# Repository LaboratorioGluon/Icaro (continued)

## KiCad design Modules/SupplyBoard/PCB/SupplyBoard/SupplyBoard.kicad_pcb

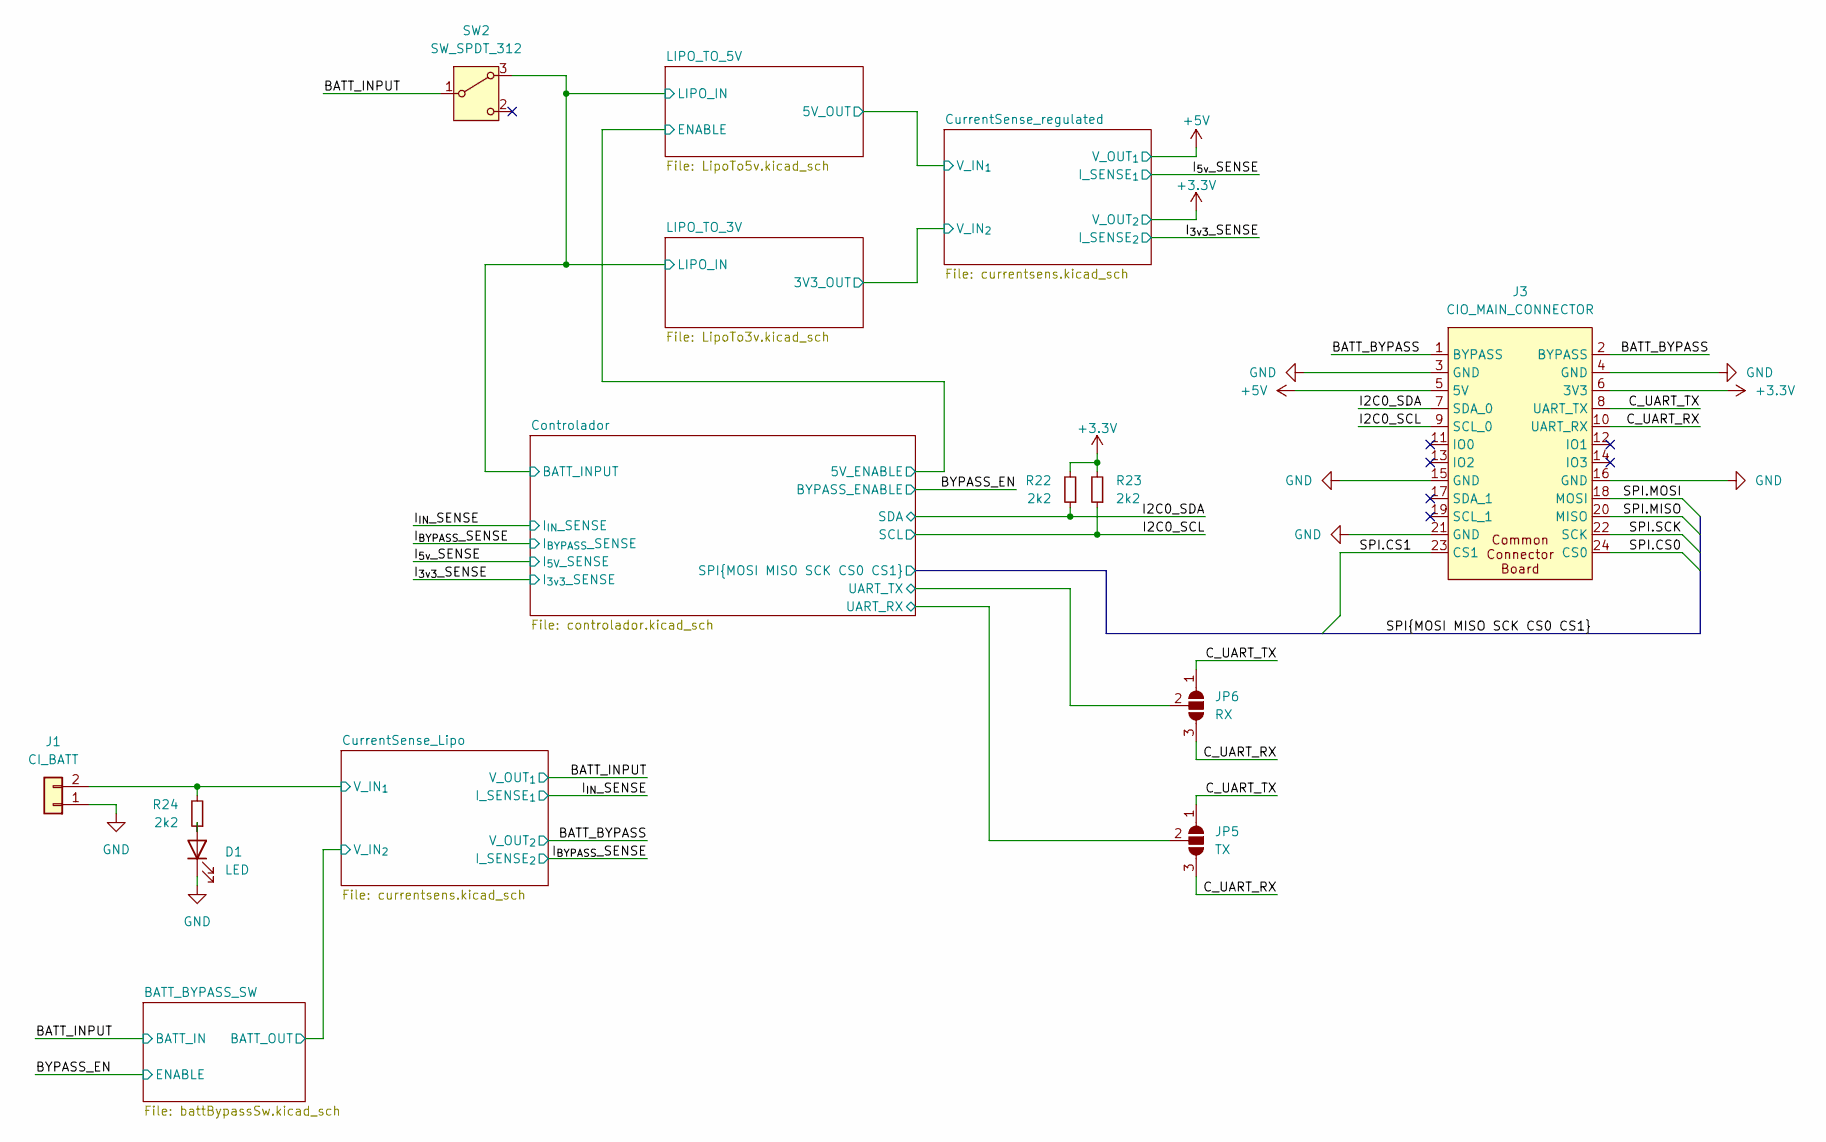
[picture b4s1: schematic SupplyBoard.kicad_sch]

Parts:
D1: LED; LED_0805_2012Metric_Pad1.15x1.40mm_HandSolder
J1: CI_BATT; AMASS_XT30U-F_1x02_P5.0mm_Vertical
J3: CIO_MAIN_CONNECTOR; Connector_Icaro_Edge_tarjeta
JP5: TX; SolderJumper-3_P1.3mm_Open_Pad1.0x1.5mm
JP6: RX; SolderJumper-3_P1.3mm_Open_Pad1.0x1.5mm
R22, R23, R24: 2k2; R_0603_1608Metric_Pad0.98x0.95mm_HandSolder
SW2: SW_SPDT_312; PinHeader_1x03_P2.00mm_Vertical

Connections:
+5V: J3.5 (5V); also elsewhere on the board
/BATT_BYPASS: J3.1 (BYPASS), J3.2 (BYPASS); also elsewhere on the board
/BATT_INPUT: SW2.1 (B); also elsewhere on the board
/C_UART_RX: J3.10 (UART_RX), JP5.3 (B), JP6.3 (B)
/C_UART_TX: J3.8 (UART_TX), JP5.1 (A), JP6.1 (A)
/Controlador/BATT_INPUT: SW2.3 (A); also elsewhere on the board
/Controlador/UART_RX: JP5.2 (C); also elsewhere on the board
/Controlador/UART_TX: JP6.2 (C); also elsewhere on the board
/CurrentSense_Lipo/V_IN_{1}: J1.2, R24.2; also elsewhere on the board
/I2C0_SCL: J3.9 (SCL_0), R23.1; also elsewhere on the board
/I2C0_SDA: J3.7 (SDA_0), R22.1; also elsewhere on the board
/SPI.CS0: J3.24 (CS0); also elsewhere on the board
/SPI.CS1: J3.23 (CS1); also elsewhere on the board
/SPI.MISO: J3.20 (MISO); also elsewhere on the board
/SPI.MOSI: J3.18 (MOSI); also elsewhere on the board
/SPI.SCK: J3.22 (SCK); also elsewhere on the board
GND: D1.1 (K), J1.1, J3.3 (GND), J3.4 (GND), J3.15 (GND), J3.16 (GND), J3.21 (GND); also elsewhere on the board
unnamed: D1.2 (A), R24.1

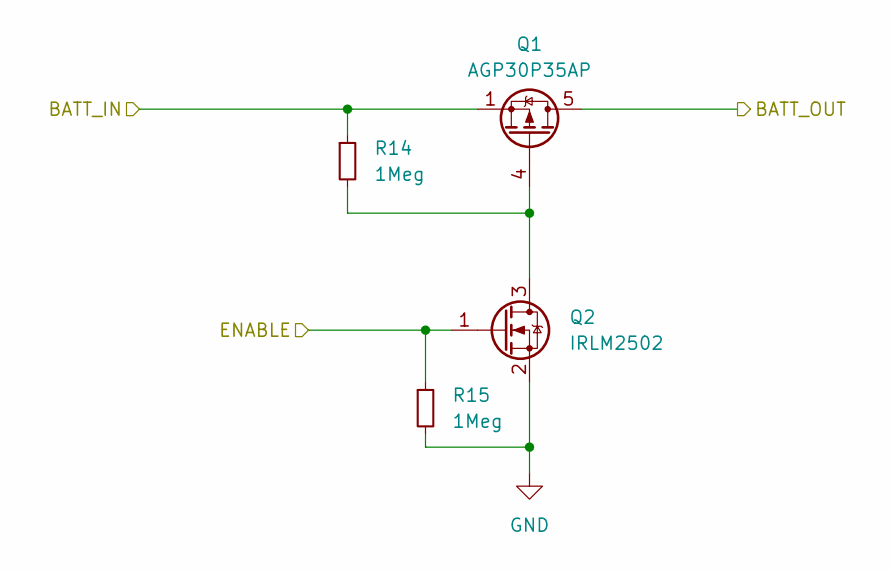
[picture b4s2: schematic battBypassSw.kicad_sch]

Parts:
Q1: AGP30P35AP; Diodes_PowerDI3333-8; LCSC C19633870
Q2: IRLM2502; SOT-23
R14, R15: 1Meg; R_0603_1608Metric_Pad0.98x0.95mm_HandSolder

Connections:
/BATT_BYPASS_SW/BATT_OUT: Q1.5 (D); also elsewhere on the board
/BATT_INPUT: Q1.1 (S), Q1.2 (S), Q1.3 (S), R14.1; also elsewhere on the board
/BYPASS_EN: Q2.1 (G), R15.1; also elsewhere on the board
GND: Q2.2 (S), R15.2; also elsewhere on the board
unnamed: Q1.4 (G), Q2.3 (D), R14.2

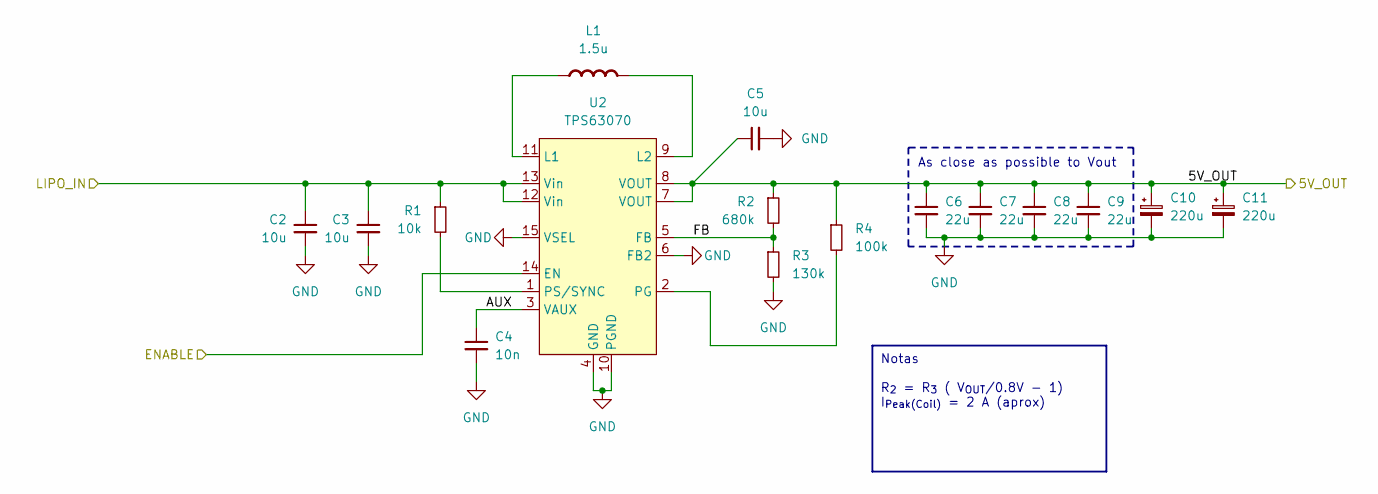
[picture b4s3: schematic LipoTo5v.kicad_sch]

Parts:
C2: 10u; C_0603_1608Metric_Pad1.08x0.95mm_HandSolder; LCSC C6119887
C3, C5: 10u; C_0603_1608Metric_Pad1.08x0.95mm_HandSolder
C4: 10n; C_0603_1608Metric_Pad1.08x0.95mm_HandSolder
C6, C7, C8, C9: 22u; C_0603_1608Metric_Pad1.08x0.95mm_HandSolder
C10, C11: 220u; CP_EIA-3216-18_Kemet-A_Pad1.58x1.35mm_HandSolder
L1: 1.5u; L_Coilcraft_XxL4040; Rating A; LCSC C5289354
R1: 10k; R_0603_1608Metric_Pad0.98x0.95mm_HandSolder
R2: 680k; R_0603_1608Metric_Pad0.98x0.95mm_HandSolder
R3: 130k; R_0603_1608Metric_Pad0.98x0.95mm_HandSolder
R4: 100k; R_0603_1608Metric_Pad0.98x0.95mm_HandSolder
U2: TPS63070; RNM0015A

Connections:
/Controlador/5V_ENABLE: U2.14 (EN); also elsewhere on the board
/Controlador/BATT_INPUT: C2.1, C3.1, R1.1, U2.12 (Vin), U2.13 (Vin); also elsewhere on the board
/LIPO_TO_5V/5V_OUT: C5.1, C6.1, C7.1, C8.1, C9.1, C10.1, C11.1, R2.1, R4.1, U2.7 (VOUT), U2.8 (VOUT); also elsewhere on the board
/LIPO_TO_5V/AUX: C4.1, U2.3 (VAUX)
/LIPO_TO_5V/FB: R2.2, R3.1, U2.5 (FB)
GND: C2.2, C3.2, C4.2, C5.2, C6.2, C7.2, C8.2, C9.2, C10.2, C11.2, R3.2, U2.4 (GND), U2.6 (FB2), U2.10 (PGND), U2.15 (VSEL); also elsewhere on the board
unnamed: L1.1 (+), U2.11 (L1)
unnamed: L1.2 (-), U2.9 (L2)
unnamed: R4.2, U2.2 (PG)
unnamed: R1.2, U2.1 (PS/SYNC)

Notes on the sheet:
As close as possible to Vout
Notas R_{2} = R_{3} ( V_{OUT}/0.8V - 1) I_{Peak(Coil)} = 2 A (aprox)

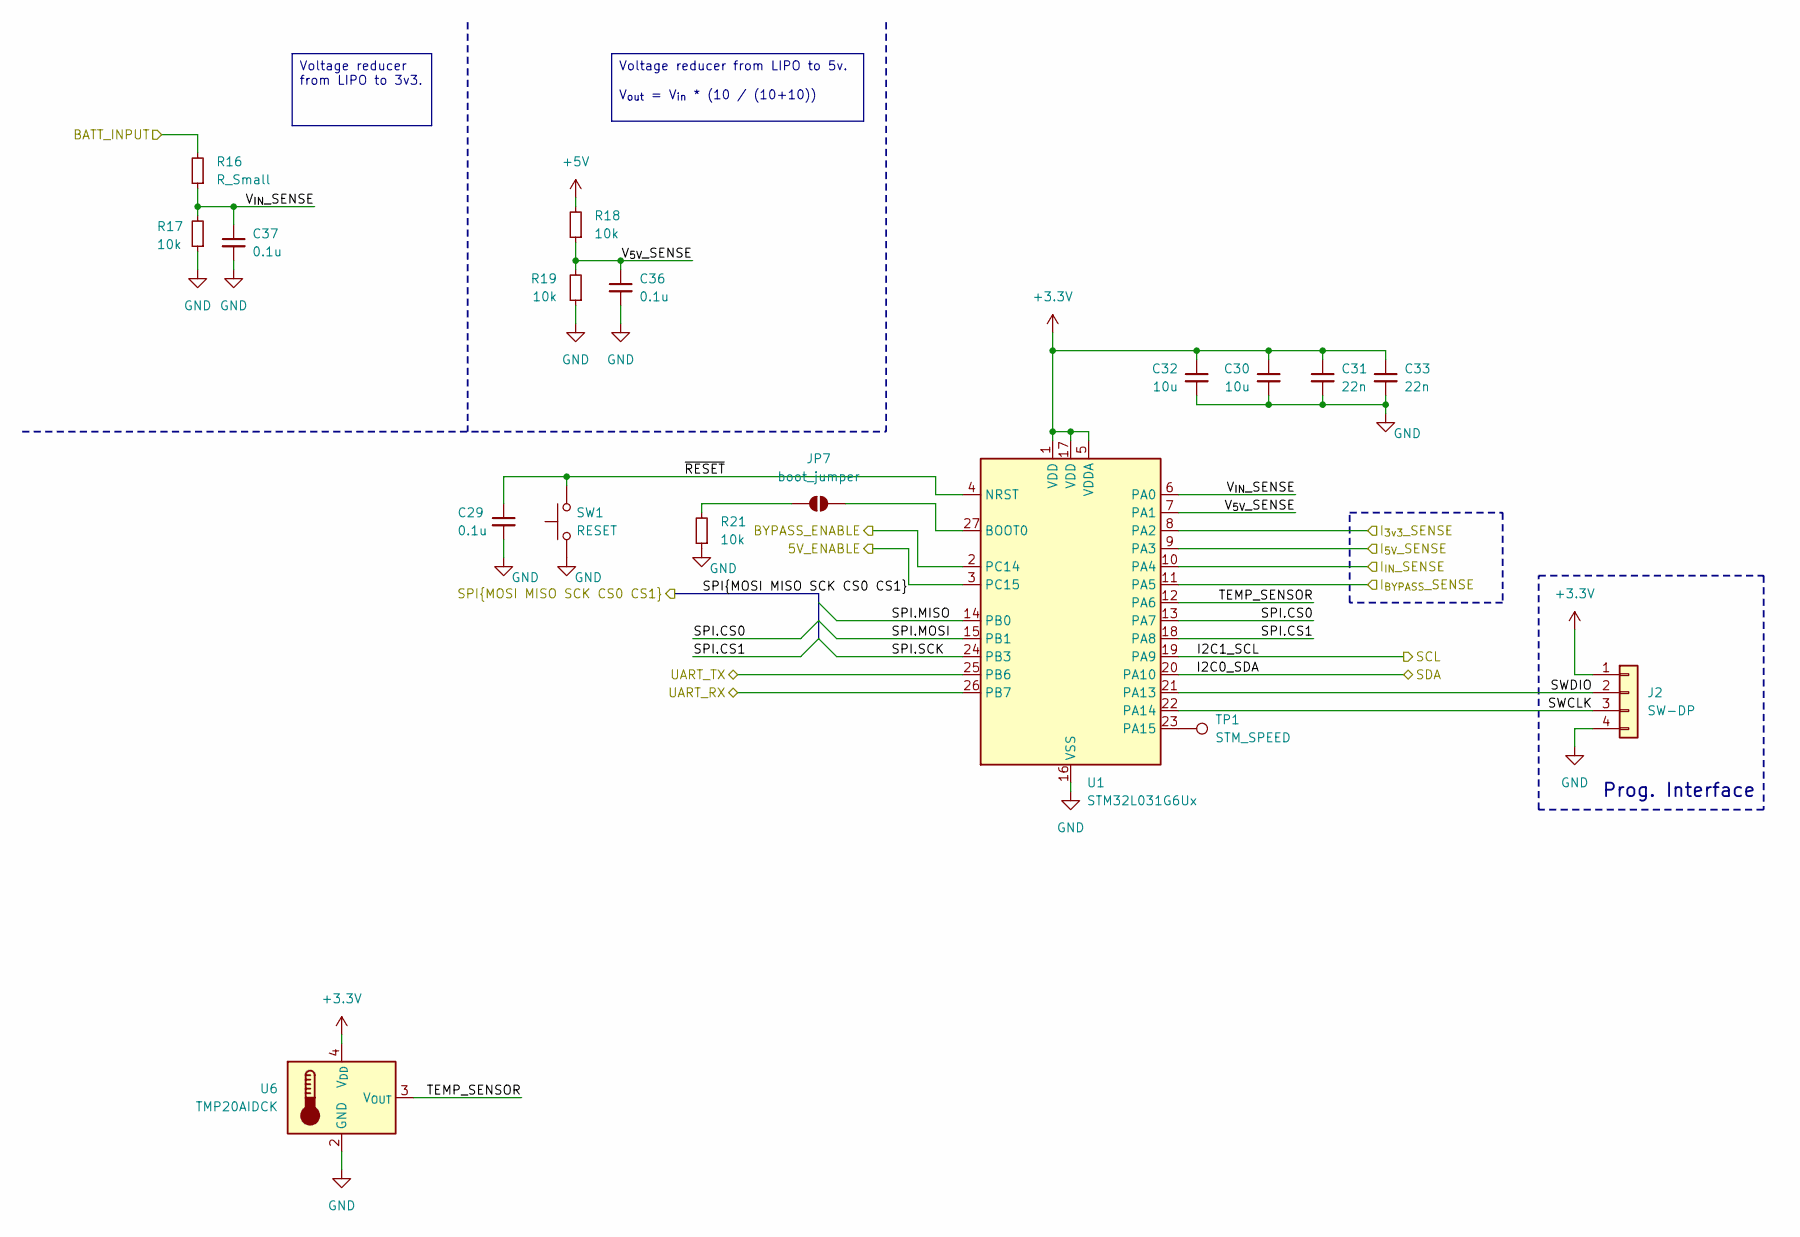
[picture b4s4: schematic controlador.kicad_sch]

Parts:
C29, C36, C37: 0.1u; C_0603_1608Metric_Pad1.08x0.95mm_HandSolder
C30, C32: 10u; C_0603_1608Metric_Pad1.08x0.95mm_HandSolder
C31, C33: 22n; C_0603_1608Metric_Pad1.08x0.95mm_HandSolder
J2: SW-DP; PinHeader_1x04_P2.54mm_Vertical
JP7: boot_jumper; SolderJumper-2_P1.3mm_Open_RoundedPad1.0x1.5mm
R16: R_Small; R_0603_1608Metric_Pad0.98x0.95mm_HandSolder
R17, R18, R19, R21: 10k; R_0603_1608Metric_Pad0.98x0.95mm_HandSolder
SW1: RESET; SideSwitch_2.7_4.65
TP1: STM_SPEED; TestPoint_Pad_D1.5mm
U1: STM32L031G6Ux; QFN-28_4x4mm_P0.5mm
U6: TMP20AIDCK; SOT-353_SC-70-5

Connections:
+5V: R18.2; also elsewhere on the board
/BYPASS_EN: U1.2 (PC14); also elsewhere on the board
/Controlador/5V_ENABLE: U1.3 (PC15); also elsewhere on the board
/Controlador/BATT_INPUT: R16.2; also elsewhere on the board
/Controlador/SWCLK: J2.3, U1.22 (PA14)
/Controlador/SWDIO: J2.2, U1.21 (PA13)
/Controlador/TEMP_SENSOR: U1.12 (PA6), U6.3 (V_{OUT})
/Controlador/UART_RX: U1.26 (PB7); also elsewhere on the board
/Controlador/UART_TX: U1.25 (PB6); also elsewhere on the board
/Controlador/V_{5V}_SENSE: C36.1, R18.1, R19.2, U1.7 (PA1)
/Controlador/V_{IN}_SENSE: C37.1, R16.1, R17.2, U1.6 (PA0)
/Controlador/~RESET: C29.1, SW1.2, U1.4 (NRST)
/I2C0_SCL: U1.19 (PA9); also elsewhere on the board
/I2C0_SDA: U1.20 (PA10); also elsewhere on the board
/I_{3v3}_SENSE: U1.8 (PA2); also elsewhere on the board
/I_{5v}_SENSE: U1.9 (PA3); also elsewhere on the board
/I_{BYPASS}_SENSE: U1.11 (PA5); also elsewhere on the board
/I_{IN}_SENSE: U1.10 (PA4); also elsewhere on the board
/SPI.CS0: U1.13 (PA7); also elsewhere on the board
/SPI.CS1: U1.18 (PA8); also elsewhere on the board
/SPI.MISO: U1.14 (PB0); also elsewhere on the board
/SPI.MOSI: U1.15 (PB1); also elsewhere on the board
/SPI.SCK: U1.24 (PB3); also elsewhere on the board
GND: C29.2, C30.2, C31.2, C32.2, C33.2, C36.2, C37.2, J2.4, R17.1, R19.1, R21.1, SW1.1, U1.16 (VSS), U1.28 (VSS), U6.2 (GND), U6.5 (GND); also elsewhere on the board
unnamed: JP7.1 (A), R21.2
unnamed: JP7.2 (B), U1.27 (BOOT0)
unnamed: TP1.1, U1.23 (PA15)

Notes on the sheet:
Prog. Interface
Voltage reducer from LIPO to 3v3.
Voltage reducer from LIPO to 5v. V_{out} = V_{in} * (10 / (10+10))

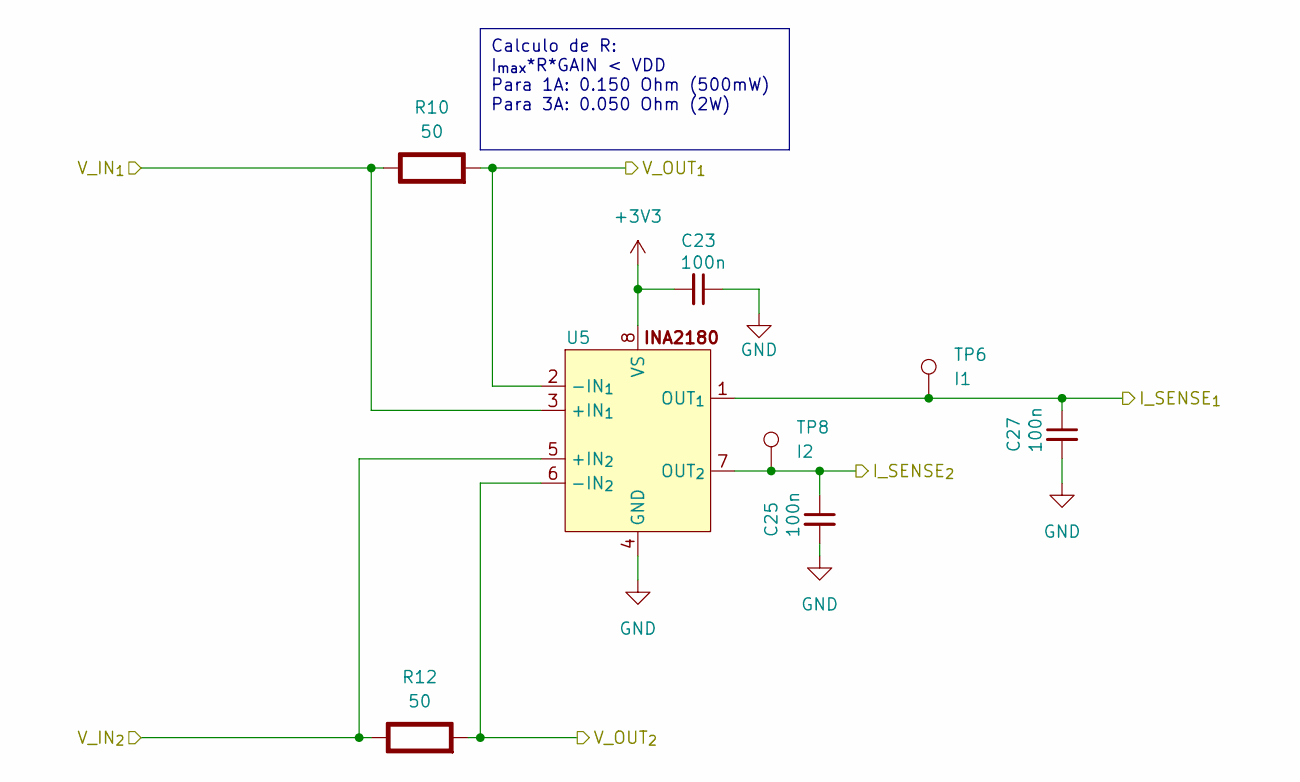
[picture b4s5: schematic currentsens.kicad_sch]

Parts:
C23, C25, C27: 100n; C_0603_1608Metric_Pad1.08x0.95mm_HandSolder
R10, R12: 50; R_2010_5025Metric_Pad1.40x2.65mm_HandSolder; Rating W
TP6: I1; TestPoint_Pad_D1.5mm
TP8: I2; TestPoint_Pad_D1.5mm
U5: VSSOP-8_3x3mm_P0.65mm

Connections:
/BATT_BYPASS: R12.2 (-), U5.6 (-IN_{2}); also elsewhere on the board
/BATT_BYPASS_SW/BATT_OUT: R12.1 (+), U5.5 (+IN_{2}); also elsewhere on the board
/BATT_INPUT: R10.2 (-), U5.2 (-IN_{1}); also elsewhere on the board
/CurrentSense_Lipo/V_IN_{1}: R10.1 (+), U5.3 (+IN_{1}); also elsewhere on the board
/I_{BYPASS}_SENSE: C25.1, TP8.1, U5.7 (OUT_{2}); also elsewhere on the board
/I_{IN}_SENSE: C27.1, TP6.1, U5.1 (OUT_{1}); also elsewhere on the board
GND: C23.1, C25.2, C27.2, U5.4 (GND); also elsewhere on the board

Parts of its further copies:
C24, C26, C28: 100n; C_0603_1608Metric_Pad1.08x0.95mm_HandSolder
R11, R13: 50; R_2010_5025Metric_Pad1.40x2.65mm_HandSolder; Rating W
TP7: I1; TestPoint_Pad_D1.5mm
TP9: I2; TestPoint_Pad_D1.5mm
U4: VSSOP-8_3x3mm_P0.65mm

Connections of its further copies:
+5V: R11.2 (-), U4.2 (-IN_{1}); also elsewhere on the board
/I_{3v3}_SENSE: C26.1, TP9.1, U4.7 (OUT_{2}); also elsewhere on the board
/I_{5v}_SENSE: C28.1, TP7.1, U4.1 (OUT_{1}); also elsewhere on the board
/LIPO_TO_3V/3V3_OUT: R13.1 (+), U4.5 (+IN_{2}); also elsewhere on the board
/LIPO_TO_5V/5V_OUT: R11.1 (+), U4.3 (+IN_{1}); also elsewhere on the board
GND: C24.1, C26.2, C28.2, U4.4 (GND); also elsewhere on the board

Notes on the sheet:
Calculo de R: I_{max}*R*GAIN < VDD Para 1A: 0.150 Ohm (500mW) Para 3A: 0.050 Ohm (2W)

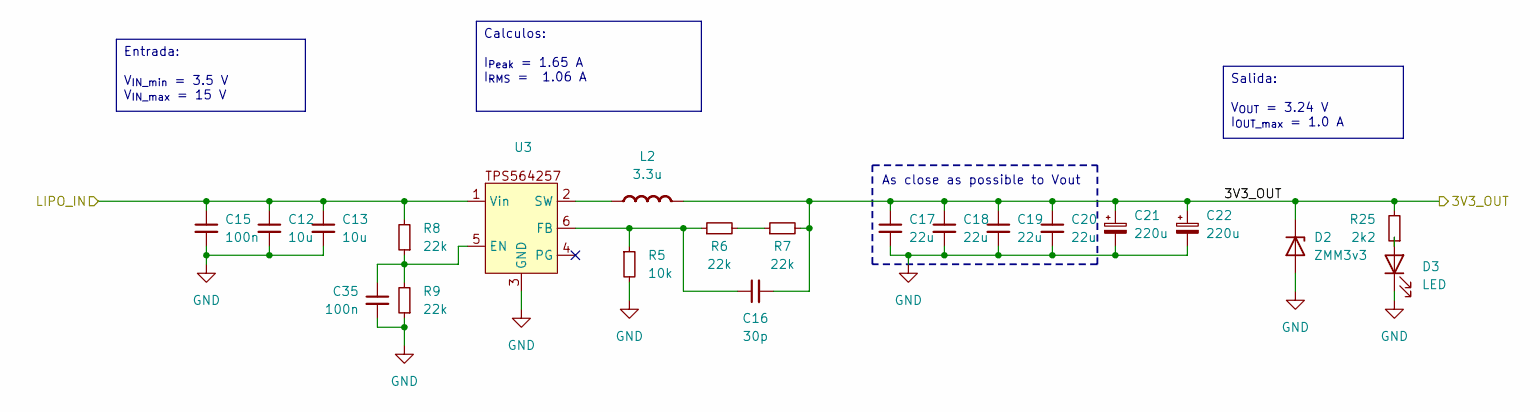
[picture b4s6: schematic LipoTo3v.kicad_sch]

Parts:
C12, C13: 10u; C_0603_1608Metric_Pad1.08x0.95mm_HandSolder
C15, C35: 100n; C_0603_1608Metric_Pad1.08x0.95mm_HandSolder
C16: 30p; C_0805_2012Metric_Pad1.18x1.45mm_HandSolder
C17, C18, C19, C20: 22u; C_0603_1608Metric_Pad1.08x0.95mm_HandSolder
C21, C22: 220u; CP_EIA-3216-18_Kemet-A_Pad1.58x1.35mm_HandSolder
D2: ZMM3v3; D_MiniMELF
D3: LED; LED_0805_2012Metric_Pad1.15x1.40mm_HandSolder
L2: 3.3u; PSPCA_D43_Series; Rating A; LCSC C436398
R5: 10k; R_0603_1608Metric_Pad0.98x0.95mm_HandSolder
R6, R7, R8, R9: 22k; R_0603_1608Metric_Pad0.98x0.95mm_HandSolder
R25: 2k2; R_0603_1608Metric_Pad0.98x0.95mm_HandSolder
U3: TPS564242DRLR_TEX; LCSC C19272233

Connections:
/Controlador/BATT_INPUT: C12.1, C13.1, C15.1, R8.2, U3.1 (Vin); also elsewhere on the board
/LIPO_TO_3V/3V3_OUT: C16.2, C17.1, C18.1, C19.1, C20.1, C21.1, C22.1, D2.1 (K), L2.2 (-), R7.2, R25.2; also elsewhere on the board
GND: C12.2, C13.2, C15.2, C17.2, C18.2, C19.2, C20.2, C21.2, C22.2, C35.2, D2.2 (A), D3.1 (K), R5.2, R9.1, U3.3 (GND); also elsewhere on the board
unnamed: D3.2 (A), R25.1
unnamed: L2.1 (+), U3.2 (SW)
unnamed: R6.2, R7.1
unnamed: C35.1, R8.1, R9.2, U3.5 (EN)
unnamed: C16.1, R5.1, R6.1, U3.6 (FB)

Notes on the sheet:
As close as possible to Vout
Salida: V_{OUT} = 3.24 V I_{OUT_max} = 1.0 A
Entrada: V_{IN_min} = 3.5 V V_{IN_max} = 15 V
Calculos: I_{Peak} = 1.65 A I_{RMS} = 1.06 A

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
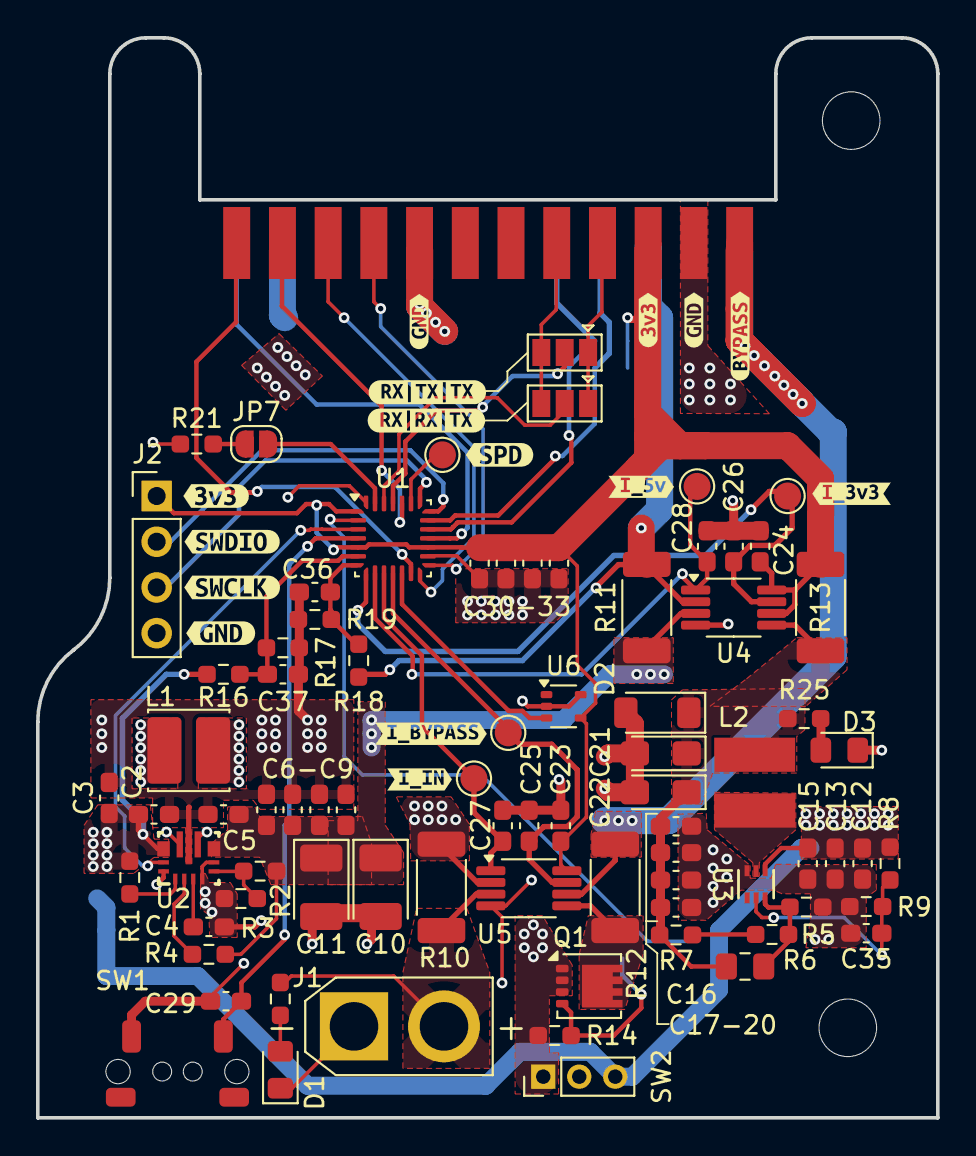
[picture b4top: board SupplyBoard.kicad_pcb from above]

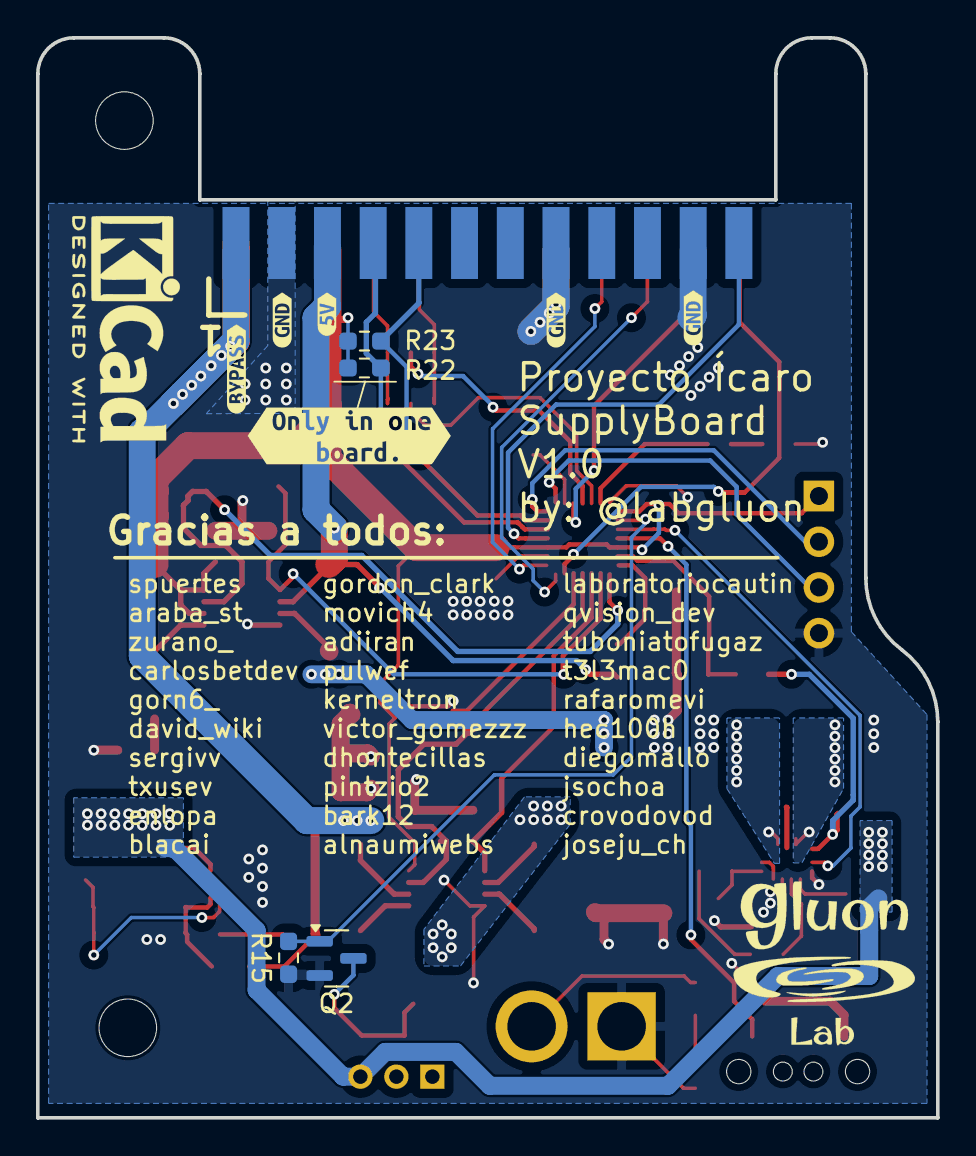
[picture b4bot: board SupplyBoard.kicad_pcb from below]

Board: 2 copper layers, 50.0 x 60.0 mm, 105 parts (11 on the bottom side), 49 nets.

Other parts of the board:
kibuzzard-67BD8B4D: G***; kibuzzard-67BD8B4D
kibuzzard-67BD8B9D, kibuzzard-67BD8B9D#2: G***; kibuzzard-67BD8B9D
kibuzzard-67BD8B63: G***; kibuzzard-67BD8B63
kibuzzard-67BD8B96: G***; kibuzzard-67BD8B96
kibuzzard-67BD8BAB, kibuzzard-67BD8BAB#2: G***; kibuzzard-67BD8BAB
kibuzzard-67BD8C4F, kibuzzard-67BD8C4F#2, kibuzzard-67BD8C4F#3: G***; kibuzzard-67BD8C4F
kibuzzard-67BD8C21: G***; kibuzzard-67BD8C21
kibuzzard-67BD8EAE: G***; kibuzzard-67BD8EAE
kibuzzard-67BD8EBE: G***; kibuzzard-67BD8EBE
kibuzzard-67BD8ECC: G***; kibuzzard-67BD8ECC
kibuzzard-67BD8EE5: G***; kibuzzard-67BD8EE5
kibuzzard-67BD90D0: G***; kibuzzard-67BD90D0
kibuzzard-67BD90D4: G***; kibuzzard-67BD90D4
kibuzzard-67BD90DE: G***; kibuzzard-67BD90DE
kibuzzard-67BD90E3: G***; kibuzzard-67BD90E3
kibuzzard-67BD93F4: G***; kibuzzard-67BD93F4
kibuzzard-67BDA321: G***; kibuzzard-67BDA321

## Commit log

2025-01-20 Added gitkeep for folder structure
2025-01-21 [DOC] IMS introduction
2025-01-21 [SupplyBoard] Initialize Kicad Project
2025-01-24 Added Icaro main connector and other footprints
2025-01-24 Supply board added common connector
2025-01-24 [DOC] Minor doc improvements
2025-01-25 [Supply Board] Creados subesquemas
2025-01-25 Updated documentation
2025-01-26 Added footprints for supply board components
2025-01-26 Lipo to 3v3 circuit added
2025-01-26 Changed documentation and added LCSC to buck converter
2025-01-28 SupplyBoard - Added INA2180 current sensor
2025-02-01 Added current sensor
2025-02-01 Added First version of IMS
2025-02-11 Supply board schematic and PCB
2025-02-18 Initial sensor board template
2025-02-23 sensor board basic components
2025-02-23 Modified gitignore to avoid zip files
2025-02-23 Updated supply board for v2, and BMP280 tinkering project
2025-02-23 Actualizado el README.md
2025-02-26 Muchas cosas: Backplane, SupplyBoard y principio SensorBoard
2025-02-26 Finished Supply board
2025-02-27 Organizadas resistencias y condensador / Enrutado
2025-02-27 Guardando cambios
2025-02-27 Agregando nuevas carpetas de PCB
2025-03-03 Enrutado de diseño de PT100 en la sensorboard
2025-03-07 Add multiple placeholders for the functionality to be implemented.
2025-03-07 Change icon
2025-03-07 Create pages for each functionality
2025-03-08 Map page: Add reset position button, add bottom sheet for information and reset button.
2025-03-08 Add data retrieve from web api
2025-03-08 Add tracking switch (tracking not implemented) Add data table with data streaming from ISS position web api,
2025-03-08 Refactor detail view
2025-03-08 Create service for ISS data streams.
2025-03-08 Move camera and marker following ISS
2025-03-08 Add animation for map camera movement
2025-03-09 Create service directopry in common to make services available globally. Cleanng and renaming of map page Create a todo/ideas list for changes
2025-03-09 Finished Sensor and Backplane boards
2025-03-11 [WIP] Working on path etrapolation for marker tracker
2025-03-13 Add precise precition by extrapolating lat/lon.
2025-03-15 Added MKDocs library to deploy the documentation on a webpage on GitHub
2025-03-15 Updated gitignore
2025-03-15 Updated docs in MkDocs
2025-03-15 Update ci.yml
    Added develop to mkdocs CI
2025-03-15 Update Bluesky link in navigation
2025-03-15 Update MKDocs format for autoformating mutliple languages
2025-03-15 Update requirements.txt missed i18n dependency
2025-03-16 Updated Doc for Supply Board
2025-03-16 Added components to SupplyBoard hardware
2025-03-16 Deployed bf95f5e with MkDocs version: 1.6.1
2025-03-16 Working GPIO and ADC
2025-03-16 Working UART
2025-03-16 Added temperature to lib
2025-03-18 Move satellite data class to data directory
2025-03-23 Create LICENSE
2025-03-23 Modified README.md for Markdown Readability and Icon for MKDocs
2025-03-23 Added Favicon
2025-03-23 Added custom colors
2025-03-23 Added custom colors (HEX FORMAT)
2025-03-24 Modified `primary color` on dark mode from amber to orange
    In `mkdocs.yml``file
2025-03-24 Added new Documentation from `Docs` folder and translated
2025-03-24 Missed
2025-03-24 Working STM32, and SensorBoard: BME, BMI, PT100 and GPS
2025-03-24 Fix typo formatting in docs
2025-03-24 Add SX1278 lib
2025-03-24 Initial state Communication Board
2025-03-28 Improve ISS tracking, request 2 times at start with period of 1 second, then request every 10 seconds and extrapolate in between every 200ms
2025-03-28 Add temperature widget for external and internal temperatures
2025-03-28 Add scrolling to sensors page
2025-03-28 Implement 3-axis widget for accelerometer and gyroscope
2025-03-28 Remove animation from temperature widget,
2025-03-28 Create first version for sensors page and sensors simulated service
2025-03-28 Edit sensor data simulation service for more frequency
2025-03-28 Fix reference to sensorpage
2025-03-28 Fix three axis widget
2025-03-28 Rename temperature labels
2025-03-28 Improve temperature by making it generic to any double data source.
2025-03-28 Enable small vertical screen
2025-03-28 Add ignore known warnings
2025-03-28 Implement humidity widget.
2025-03-28 Tweak generation of sensor data
2025-03-30 Updated GPS code
2025-04-02 First working version of CommunicationBoard library with dummy message
2025-04-06 Add E22-900M30S module to Icaro lib
2025-04-06 Update Communication Board with E22-900M30S module
2025-04-07 First PCB layout version
2025-04-07 Change solder jumper from close to open
2025-04-09 First PCBA with ESP32
2025-04-13 Many many things
2025-04-14 CommsBoard v1.0
2025-04-18 Add Camera Board software project
2025-04-18 Change speed to 240MHz
2025-04-18 Configure QIO flash mode
2025-04-18 Add esp32-camera submodule
2025-04-18 Testing camera and sd card.
2025-04-18 Implement SDCard interface.
2025-04-18 Implement OV2640 interface Remove camera support for not used cameras to reduce code size. Increase max log level Ignore vscode settings file
2025-04-18 Fix device constructors
2025-04-19 Wifi connection implemented (TODO: Connection and data transfers)
2025-04-19 Added private keyword
2025-04-19 Remove INetwork interface
2025-04-19 Add Secrets file to gitignore
2025-04-19 Add partitions for ESP32-S3 (N16R8)
2025-04-19 Change udp/tcp to socket class Fix destructor call for unique_ptr sockets
2025-04-19 Change destructors to virutal destructors
2025-04-19 temp
2025-04-19 Cleaning: * Comment static mode of wifi packet * Remove includes * Restore commented initializations
2025-05-01 Code to capture frame and store in SDCard
2025-05-01 Add expected sequence diagram to doc
2025-05-02 Change default channel to 13 Fix Max payload size limit for wifiraw Change LWIP, TCPIP and Camera affinity to core 1
2025-05-02 Refactor code to split Storing images and sending data to different threads Use of shared_ptr instead of simple c pointers
2025-05-02 Add LLC header to wifiraw sending
2025-05-02 Improve 802.11 headers generation to avoid memory allocation and memory copies
2025-05-02 Modify SDCard log level
2025-05-02 Implement sending bigger size messages: * Add message fragmentation header
2025-05-02 Send image frame Fix data sending duplicated data
2025-05-02 Send each image only once Use 2 frame buffers for each thread
2025-05-02 Remove unused code
2025-05-03 Add helper scripts for data reception
2025-05-03 Add tool scripts
2025-05-03 Add minor fixes/checks
2025-05-03 Add documentation
2025-05-04 Fix interface initialization script
2025-05-04 Add MAVlink library, send heartbeat every second. Refactor raw 802.11 link to make it multilink Refactor raw 802.11 link to use it in multiple threads
2025-05-04 Add MAV page and serive for data reception and representation from ESP32 in MAV format
2025-05-06 Filter received fragments to RAW_IMAGE in python script
2025-05-06 Remove MAV thread Remove Wifi, use only WifiRaw (until better solution is found) Implement MAVComponent and MAVSystem for MAV message encapsulation Implement State Machine in Main thread to control t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
2025-05-07 Fix image receiver to clean memory with fragments that will never be completed
2025-05-07 Add cameras status to mav page
2025-05-08 Add setting channel to interface initialization script
2025-05-08 Split and improve forwarder scripts: * Add thread supervisor and recovery * Add MJPEG server
2025-05-08 * Implement mav camera component * Add camera notification when image is captured by stream and store threads *Limit stream and store threads cycles per second
2025-05-11 Implement camera view as a Mjpeg client, this needs a mjpeg server in localhost
2025-05-11 Add image captured coordinates if available
2025-05-11 Move camera page widget to own directory
2025-05-11 Implement app settings page, Add camera settings and connect to camera page
2025-05-11 Fix sensor page not filling content container
2025-05-11 Add button to manually manage navigation panel extension
2025-05-13 Add I2CSlave class (read only) and thread to test it
2025-05-13 [TO BE TESTED] Add IMS messages reception Add definition for some IMS messages and tags Share received IMS data to all threads
2025-05-13 Add proposal for ims_messages asserts and raw message
2025-05-15 Add pack attribute to IMS message substruct (doing some testing sub struct was not being packed) Add static assert to force compile size check of message data Add raw usable message in
2025-05-15 Add IMS Messages fixes
2025-05-16 Many changes on supply board SW&HW
2025-05-16 Add messages to i2c slave reception Add message generator in python (for raspberry pi)
2025-05-16 Update system time with i2c received message
2025-05-17 Modify GPS data to double instead of float Change i2cSlave terminology to i2cListener
2025-05-17 Fix MAV data conversions Add GUI to send messages to the ESP32 through I2C Fix i2C master simulator messages to use doubles for lat/lon/alt
2025-05-17 Reorder pages Add MAV reception of GPS and IMU data messages Add MAV sensors page for data received from MAV link Add MAV map page for data received from MAV link
2025-05-17 Display tracking switch on mav map page
2025-05-18 Add reception for more MAV messages, Fix MAV message parsing
2025-05-18 Move common widgets to common directory
2025-05-18 Add power widget to MAV page
2025-05-18 Replace coverage text for widget icons
2025-05-18 Move summary to independent widget, add it to main instead of sensors
2025-05-18 Fix library commit for mavlink lib Add data messages to python i2c master simulator Increase stack for main task Add MAV messages to ESP32 for sensors, battery and time
2025-05-18 Send epoch time in micro seconds
2025-05-18 Add seconds to summary widget
2025-05-18 Fix home page
2025-05-18 Fix camera configuration
2025-05-18 Fix thread arguments being deleted from stack Add logs Disable logs
2025-05-20 Change mac filter to sniff library (hope is has better optimization)
2025-05-20 Add script to forward/serve images and mav messages in one script
2025-05-20 Fix I2C reception data for better message handling
2025-05-20 Move messages to Camera custom namespace
2025-05-20 Remove placeholder pages except for logs
2025-05-20 Add coordinates to camera capture notification
2025-05-20 Add Logs page
2025-05-20 Add generated plugin
2025-05-20 Fix color for logs
2025-05-24 Modify image storing: * Add directories to SDCard * Add script to prepare the SDCard This improves significantly the writting performance due to FAT FS
2025-05-24 Fix prepareSD.sh script for CameraBoard
2025-05-25 clean up
2025-05-25 Add log to file, reduce camera logs to 1 out of 10 messages received
2025-05-25 Add CRC (esp_som_crc8_le) to IMS messages, using header "dummy" field
2025-05-25 Changed MISO/MOSI in Comms
2025-06-01 Working comms with i2c
2025-06-02 Added LoRa data send by I2C to Air
2025-06-03 SensorBoard - New file every reset
2025-06-03 SupplyBoard SW version 1.0
2025-06-08 Initialization error check
2025-06-08 Files moved to single folder
2025-06-08 Remove VM dependency from app
2025-06-08 Updated Lora ksy
2025-06-10 Added mavlink to forwarder
2025-06-11 First version of system status in flutter app
2025-06-11 updated Camera for ESP32CAM
2025-06-11 Updated Supply board with VDDA and Temperature
2025-06-15 Almost ready for v1.0
2025-06-15 Deployed 016b538 with MkDocs version: 1.6.1
